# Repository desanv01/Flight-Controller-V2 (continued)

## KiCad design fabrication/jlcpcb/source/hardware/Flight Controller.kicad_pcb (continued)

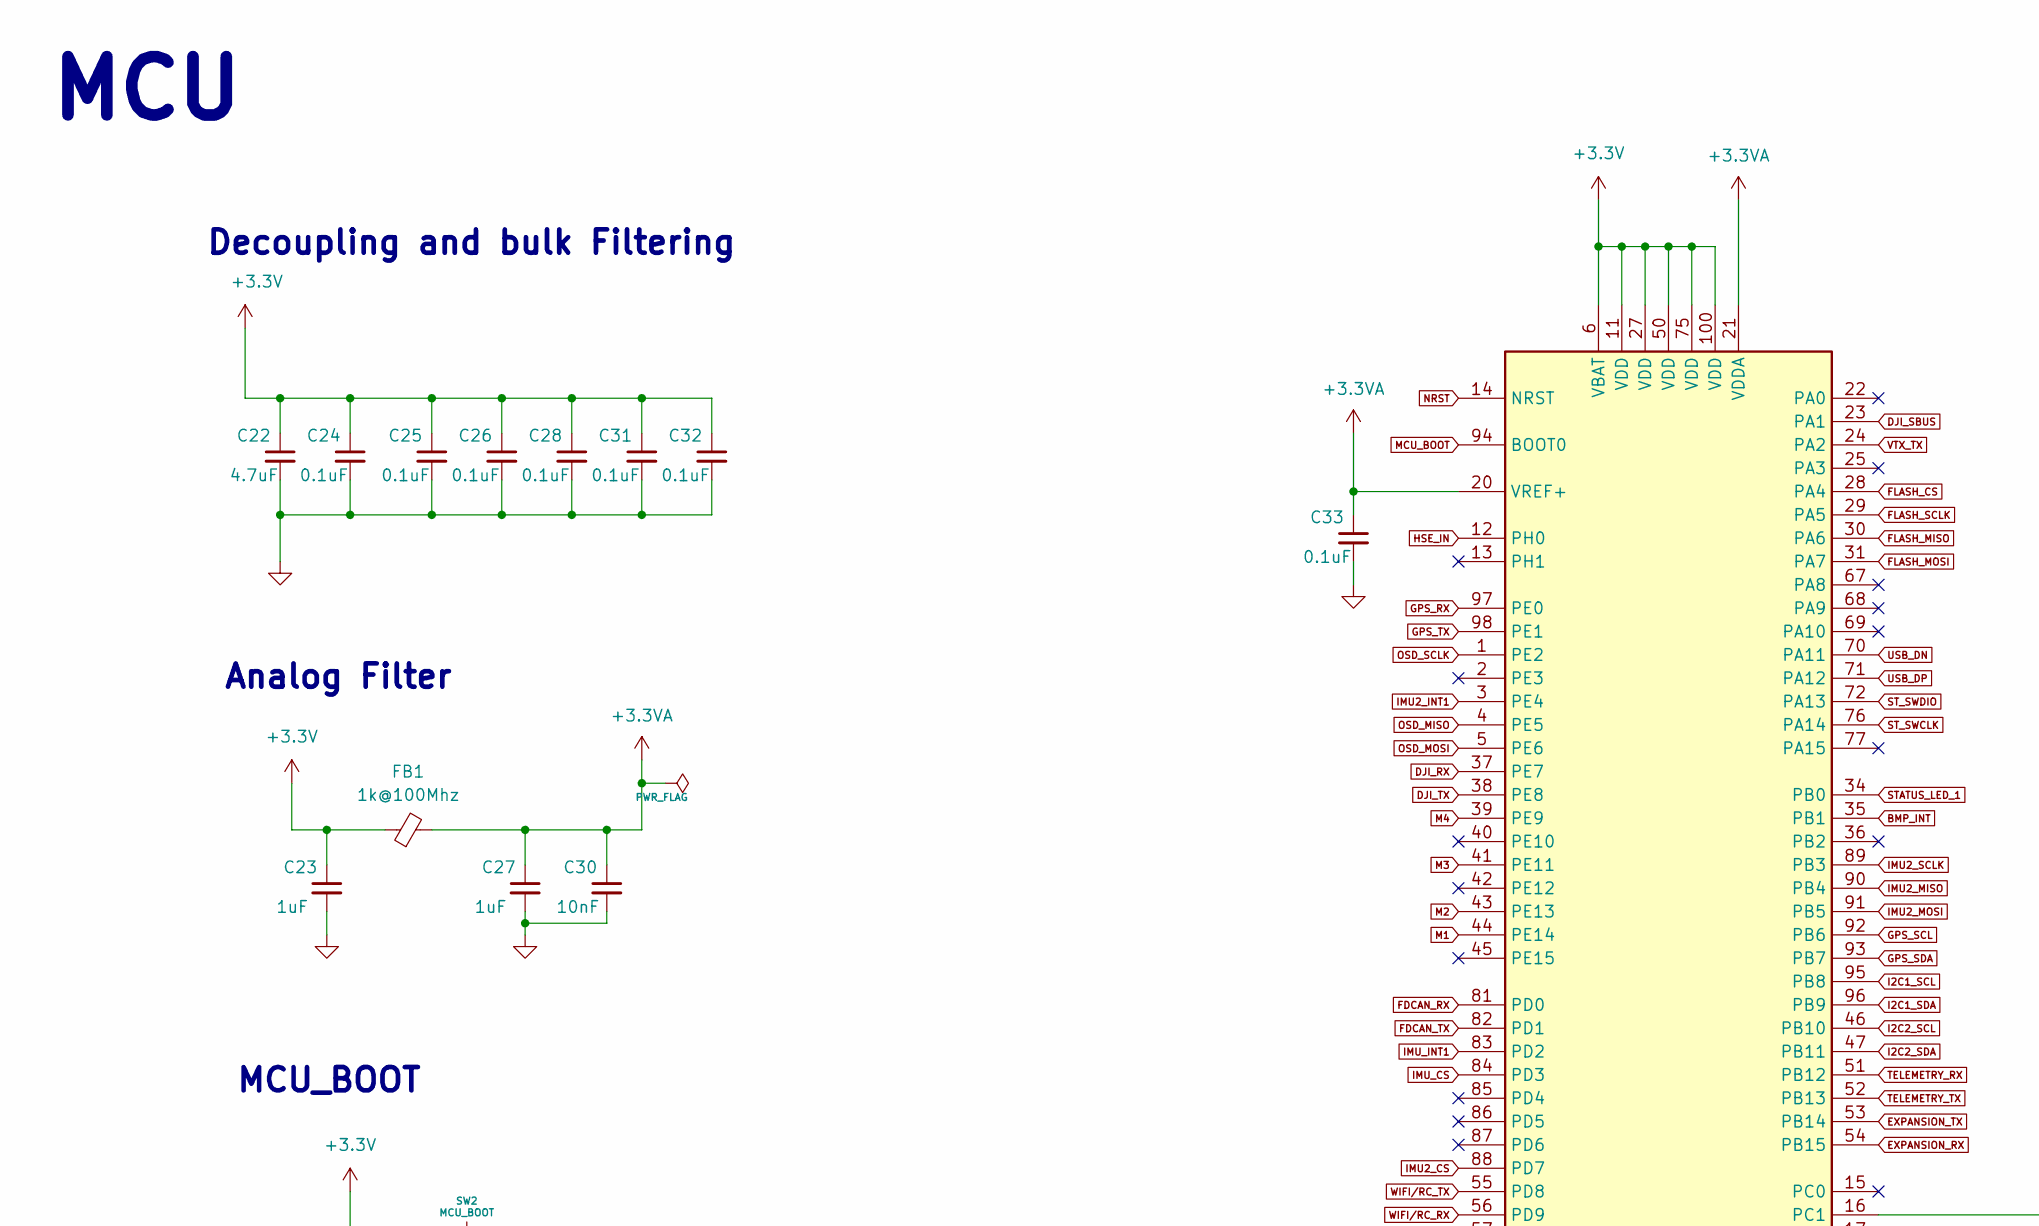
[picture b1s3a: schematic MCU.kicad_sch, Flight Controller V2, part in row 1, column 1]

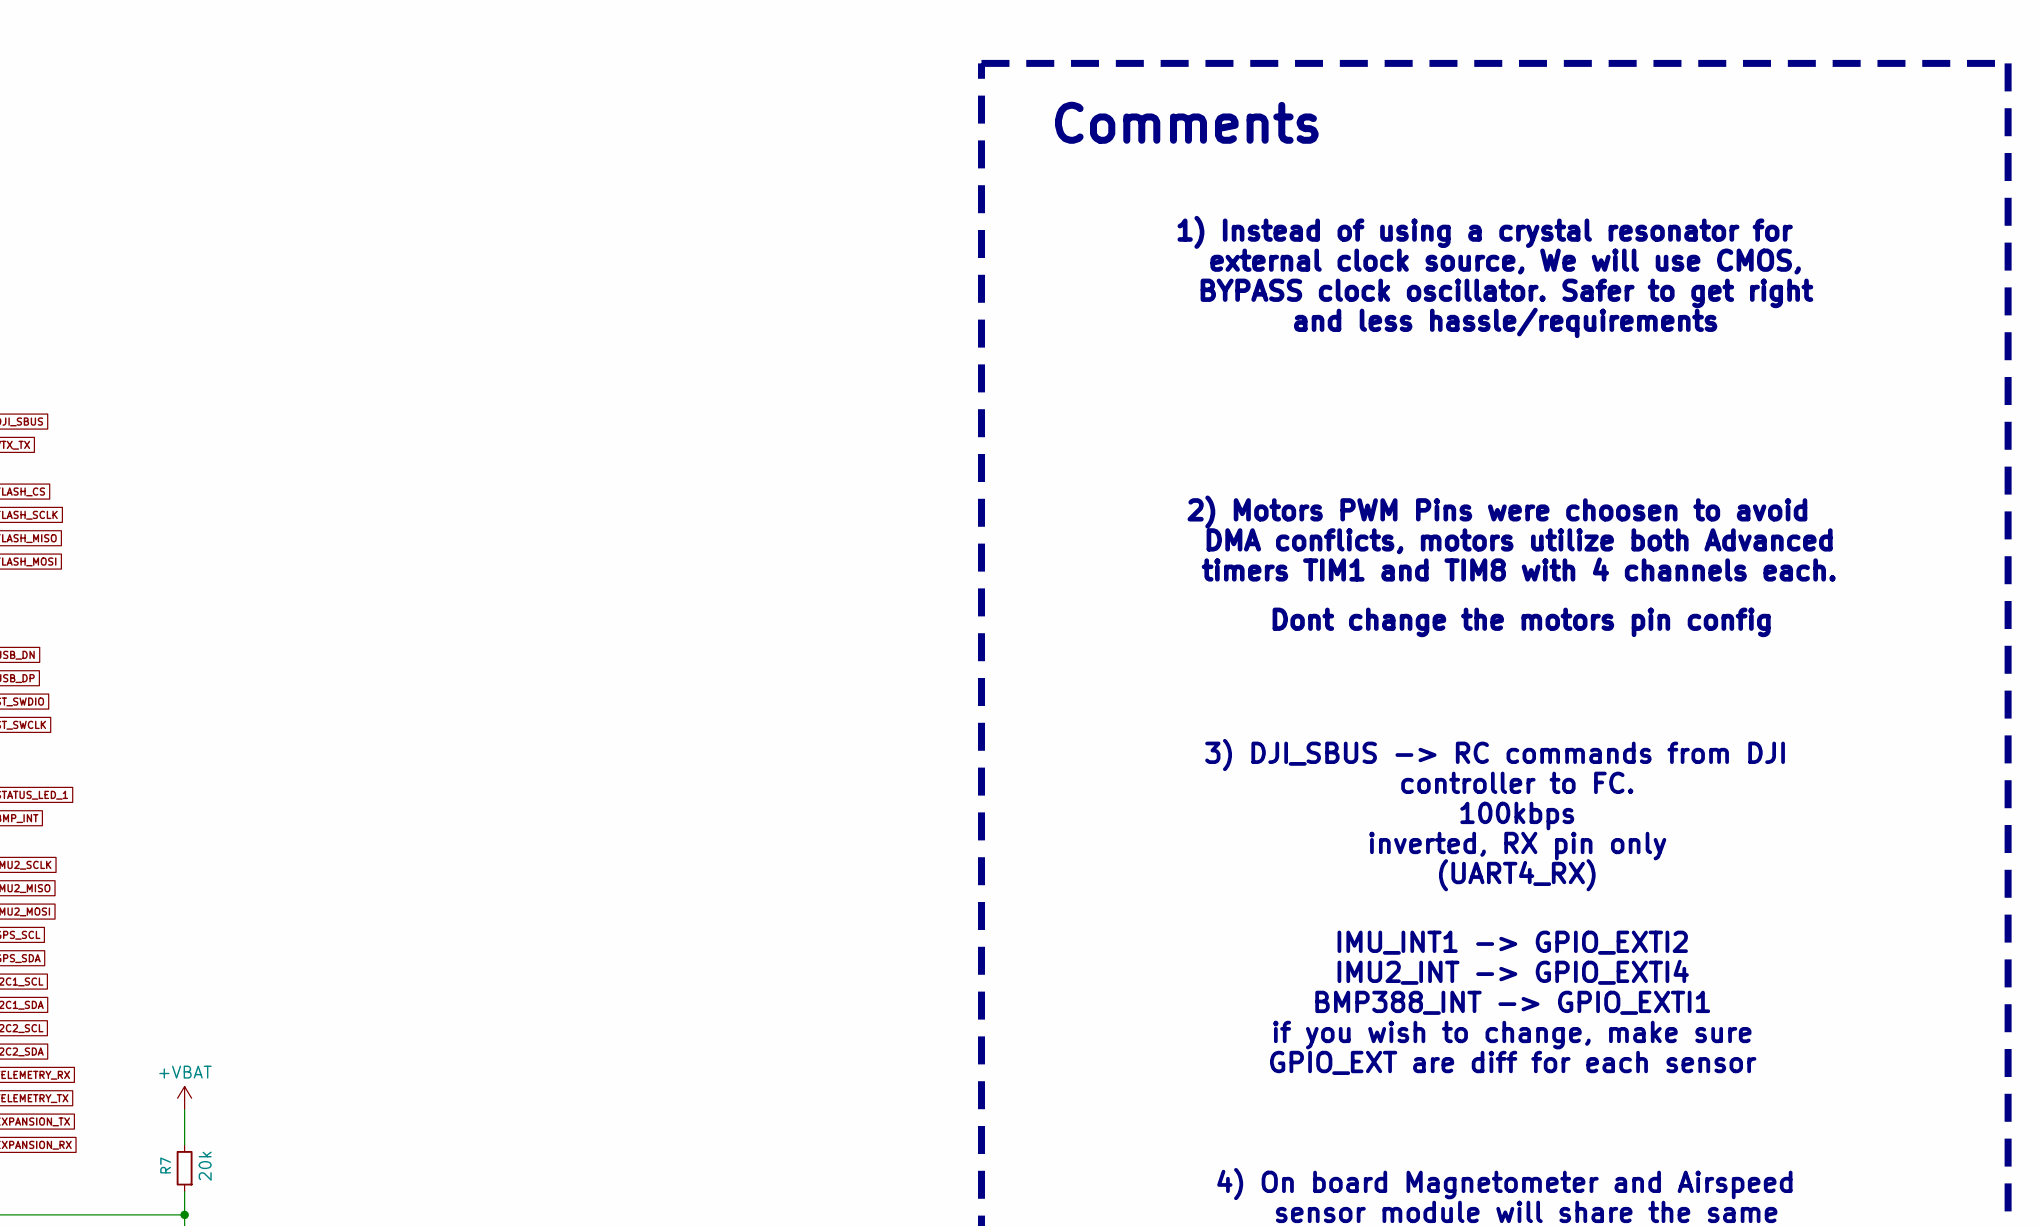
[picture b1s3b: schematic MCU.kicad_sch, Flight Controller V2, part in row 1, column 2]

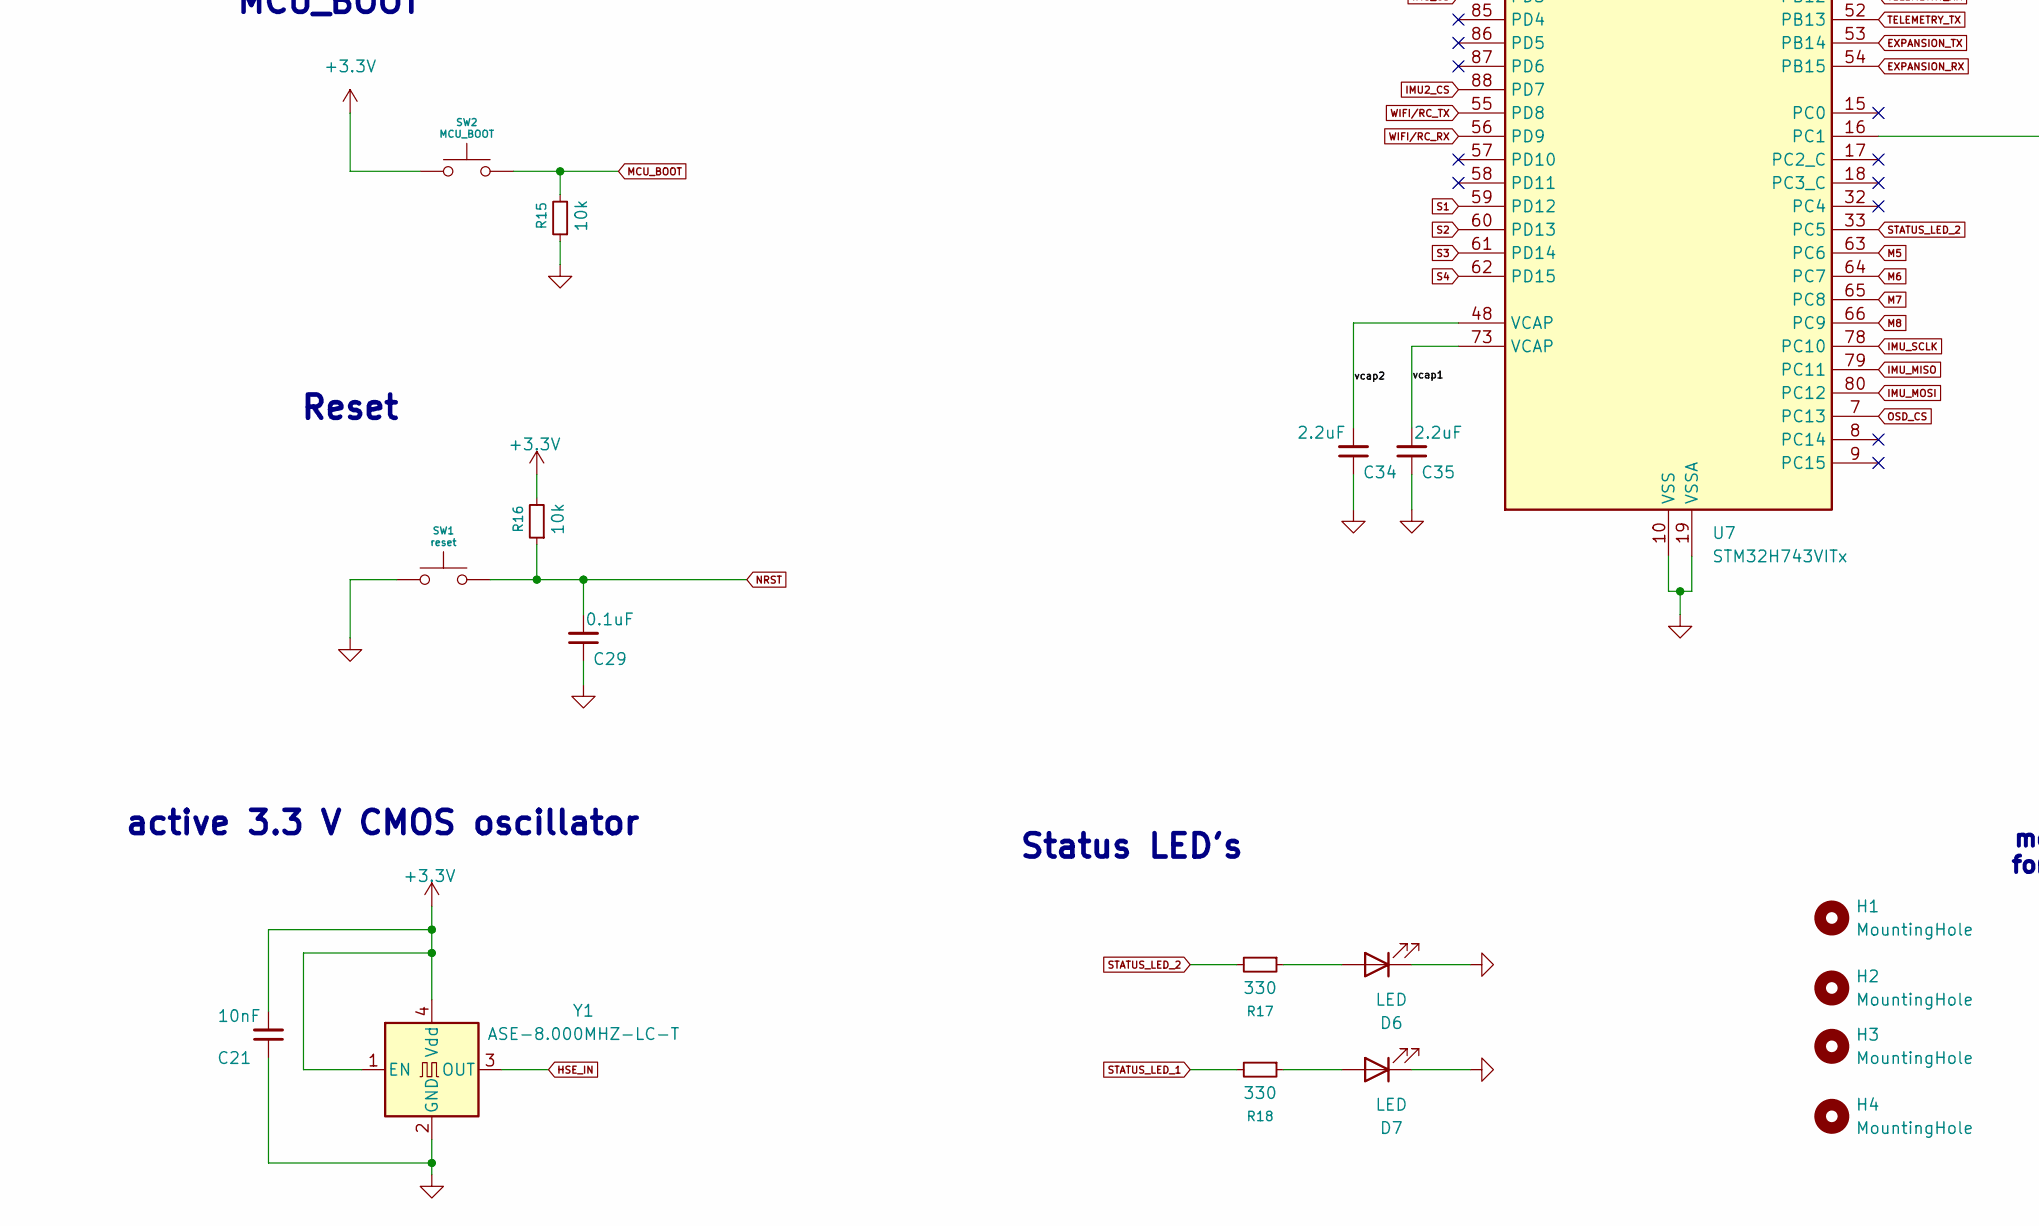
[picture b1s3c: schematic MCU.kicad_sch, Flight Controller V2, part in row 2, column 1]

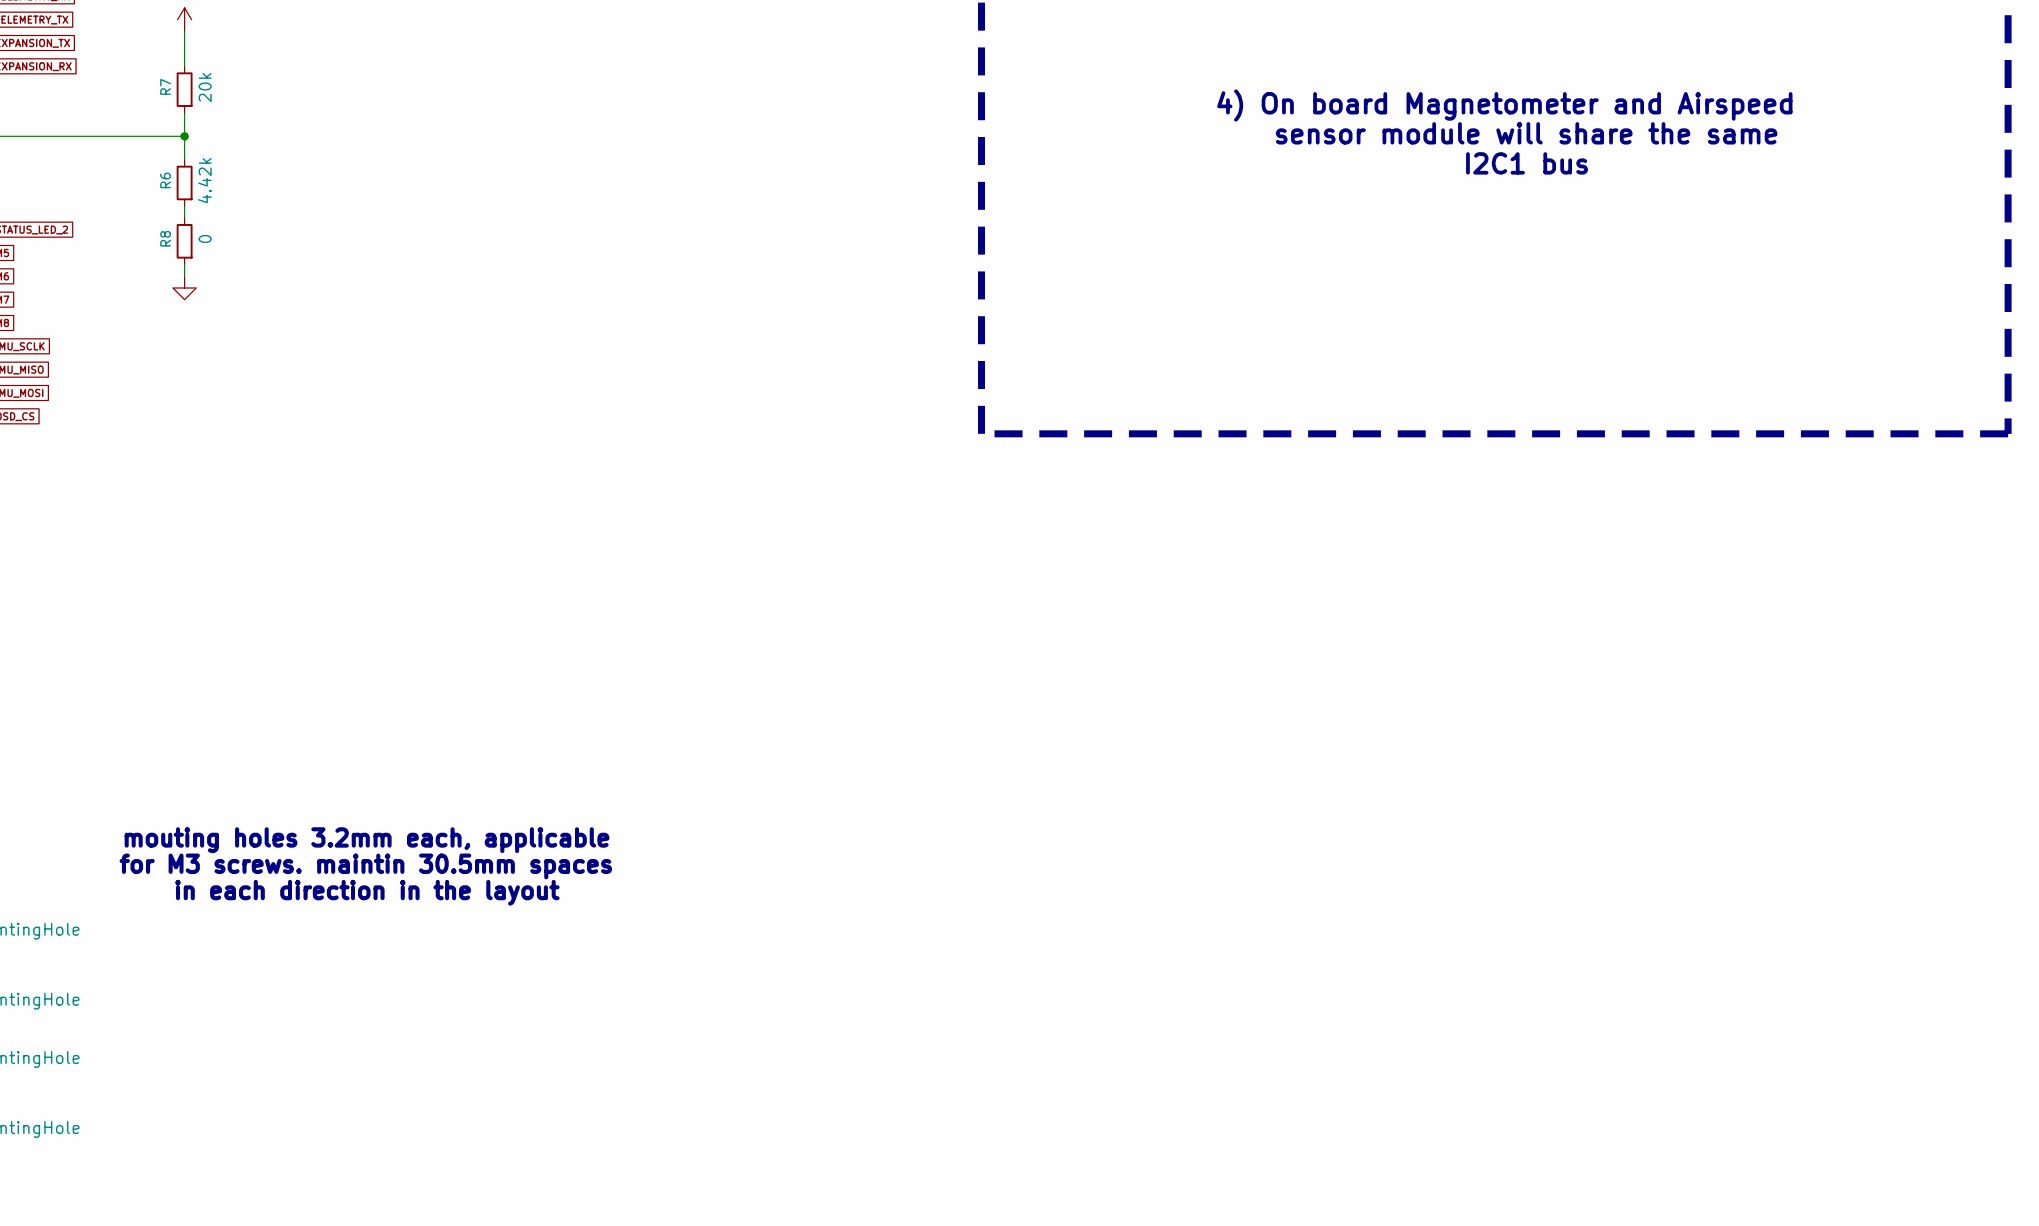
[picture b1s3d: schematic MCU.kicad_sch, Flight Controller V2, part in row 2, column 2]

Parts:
C21: 10nF; C_0603_1608Metric
C22: 4.7uF; C_0603_1608Metric
C23, C27: 1uF; C_0603_1608Metric
C24, C25, C26, C28, C29, C31, C32: 0.1uF; C_0402_1005Metric
C30: 10nF; C_0402_1005Metric
C33: 0.1uF; C_0603_1608Metric
C34, C35: 2.2uF; C_0603_1608Metric
D6, D7: LED; LED_0805_2012Metric
FB1: 1k@100Mhz; L_0603_1608Metric
H1, H2, H3, H4: MountingHole; MountingHole_3.2mm_M3_Pad_Via
R6: 4.42k; R_0402_1005Metric
R7: 20k; R_0402_1005Metric
R8: 0; R_0402_1005Metric
R15, R16: 10k; R_0402_1005Metric
R17, R18: 330; R_0402_1005Metric
SW1: reset; SW_Push_SPST_NO_Alps_SKRK
SW2: MCU_BOOT; SW_Push_SPST_NO_Alps_SKRK
U7: STM32H743VITx; LQFP-100_14x14mm_P0.5mm
Y1: ASE-8.000MHZ-LC-T; Oscillator_SMD_Abracon_ASE-4Pin_3.2x2.5mm

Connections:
+3.3V: C21.2, C22.1, C23.1, C24.1, C25.1, C26.1, C28.1, C31.1, C32.1, FB1.1, R16.2, SW2.1, U7.6 (VBAT), U7.11 (VDD), U7.27 (VDD), U7.50 (VDD), U7.75 (VDD), U7.100 (VDD), Y1.1 (EN), Y1.4 (Vdd); also elsewhere on the board
+3.3VA: C27.1, C30.1, C33.1, FB1.2, U7.20 (VREF+), U7.21 (VDDA)
+VBAT: R7.2; also elsewhere on the board
/MCU/vcap1: C35.2, U7.73 (VCAP)
/MCU/vcap2: C34.2, U7.48 (VCAP)
BMP_INT: U7.35 (PB1); also elsewhere on the board
DJI_RX: U7.37 (PE7); also elsewhere on the board
DJI_SBUS: U7.23 (PA1); also elsewhere on the board
DJI_TX: U7.38 (PE8); also elsewhere on the board
EXPANSION_RX: U7.54 (PB15); also elsewhere on the board
EXPANSION_TX: U7.53 (PB14); also elsewhere on the board
FDCAN_RX: U7.81 (PD0); also elsewhere on the board
FDCAN_TX: U7.82 (PD1); also elsewhere on the board
FLASH_CS: U7.28 (PA4); also elsewhere on the board
FLASH_MISO: U7.30 (PA6); also elsewhere on the board
FLASH_MOSI: U7.31 (PA7); also elsewhere on the board
FLASH_SCLK: U7.29 (PA5); also elsewhere on the board
GND: C21.1, C22.2, C23.2, C24.2, C25.2, C26.2, C27.2, C28.2, C29.1, C30.2, C31.2, C32.2, C33.2, C34.1, C35.1, D6.1 (K), D7.1 (K), R8.1, R15.1, SW1.1, U7.10 (VSS), U7.19 (VSSA), U7.26 (VSS), U7.49 (VSS), U7.74 (VSS), U7.99 (VSS), Y1.2 (GND); also elsewhere on the board
GPS_RX: U7.97 (PE0); also elsewhere on the board
GPS_SCL: U7.92 (PB6); also elsewhere on the board
GPS_SDA: U7.93 (PB7); also elsewhere on the board
GPS_TX: U7.98 (PE1); also elsewhere on the board
HSE_IN: U7.12 (PH0), Y1.3 (OUT)
I2C1_SCL: U7.95 (PB8); also elsewhere on the board
I2C1_SDA: U7.96 (PB9); also elsewhere on the board
I2C2_SCL: U7.46 (PB10); also elsewhere on the board
I2C2_SDA: U7.47 (PB11); also elsewhere on the board
IMU2_CS: U7.88 (PD7); also elsewhere on the board
IMU2_INT1: U7.3 (PE4); also elsewhere on the board
IMU2_MISO: U7.90 (PB4); also elsewhere on the board
IMU2_MOSI: U7.91 (PB5); also elsewhere on the board
IMU2_SCLK: U7.89 (PB3); also elsewhere on the board
IMU_CS: U7.84 (PD3); also elsewhere on the board
IMU_INT1: U7.83 (PD2); also elsewhere on the board
IMU_MISO: U7.79 (PC11); also elsewhere on the board
IMU_MOSI: U7.80 (PC12); also elsewhere on the board
IMU_SCLK: U7.78 (PC10); also elsewhere on the board
M1: U7.44 (PE14); also elsewhere on the board
M2: U7.43 (PE13); also elsewhere on the board
M3: U7.41 (PE11); also elsewhere on the board
M4: U7.39 (PE9); also elsewhere on the board
M5: U7.63 (PC6); also elsewhere on the board
M6: U7.64 (PC7); also elsewhere on the board
M7: U7.65 (PC8); also elsewhere on the board
M8: U7.66 (PC9); also elsewhere on the board
MCU_BOOT: R15.2, SW2.2, U7.94 (BOOT0)
NRST: C29.2, R16.1, SW1.2, U7.14 (NRST)
unnamed: D6.2 (A), R17.1
unnamed: D7.2 (A), R18.1
unnamed: R6.1, R8.2
unnamed: R6.2, R7.1, U7.16 (PC1)
OSD_CS: U7.7 (PC13); also elsewhere on the board
OSD_MISO: U7.4 (PE5); also elsewhere on the board
OSD_MOSI: U7.5 (PE6); also elsewhere on the board
OSD_SCLK: U7.1 (PE2); also elsewhere on the board
S1: U7.59 (PD12); also elsewhere on the board
S2: U7.60 (PD13); also elsewhere on the board
S3: U7.61 (PD14); also elsewhere on the board
S4: U7.62 (PD15); also elsewhere on the board
STATUS_LED_1: R18.2, U7.34 (PB0)
STATUS_LED_2: R17.2, U7.33 (PC5)
ST_SWCLK: U7.76 (PA14); also elsewhere on the board
ST_SWDIO: U7.72 (PA13); also elsewhere on the board
TELEMETRY_RX: U7.51 (PB12); also elsewhere on the board
TELEMETRY_TX: U7.52 (PB13); also elsewhere on the board
USB_DN: U7.70 (PA11); also elsewhere on the board
USB_DP: U7.71 (PA12); also elsewhere on the board
VTX_TX: U7.24 (PA2); also elsewhere on the board
WIFI/RC_RX: U7.56 (PD9); also elsewhere on the board
WIFI/RC_TX: U7.55 (PD8); also elsewhere on the board

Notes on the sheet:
Analog Filter
Reset
4) On board Magnetometer and Airspeed sensor module will share the same I2C1 bus
mouting holes 3.2mm each, applicable for M3 screws. maintin 30.5mm spaces in each direction in the layout
1) Instead of using a crystal resonator for external clock source, We will use CMOS, BYPASS clock oscillator. Safer to get right and less hassle/requirements
Comments
MCU
2) Motors PWM Pins were choosen to avoid DMA conflicts, motors utilize both Advanced timers TIM1 and TIM8 with 4 channels each.
3) DJI_SBUS -> RC commands from DJI controller to FC. 100kbps inverted, RX pin only (UART4_RX)
MCU_BOOT
active 3.3 V CMOS oscillator
IMU_INT1 -> GPIO_EXTI2 IMU2_INT -> GPIO_EXTI4 BMP388_INT -> GPIO_EXTI1 if you wish to change, make sure GPIO_EXT are diff for each sensor
Dont change the motors pin config
Decoupling and bulk Filtering
Status LED's

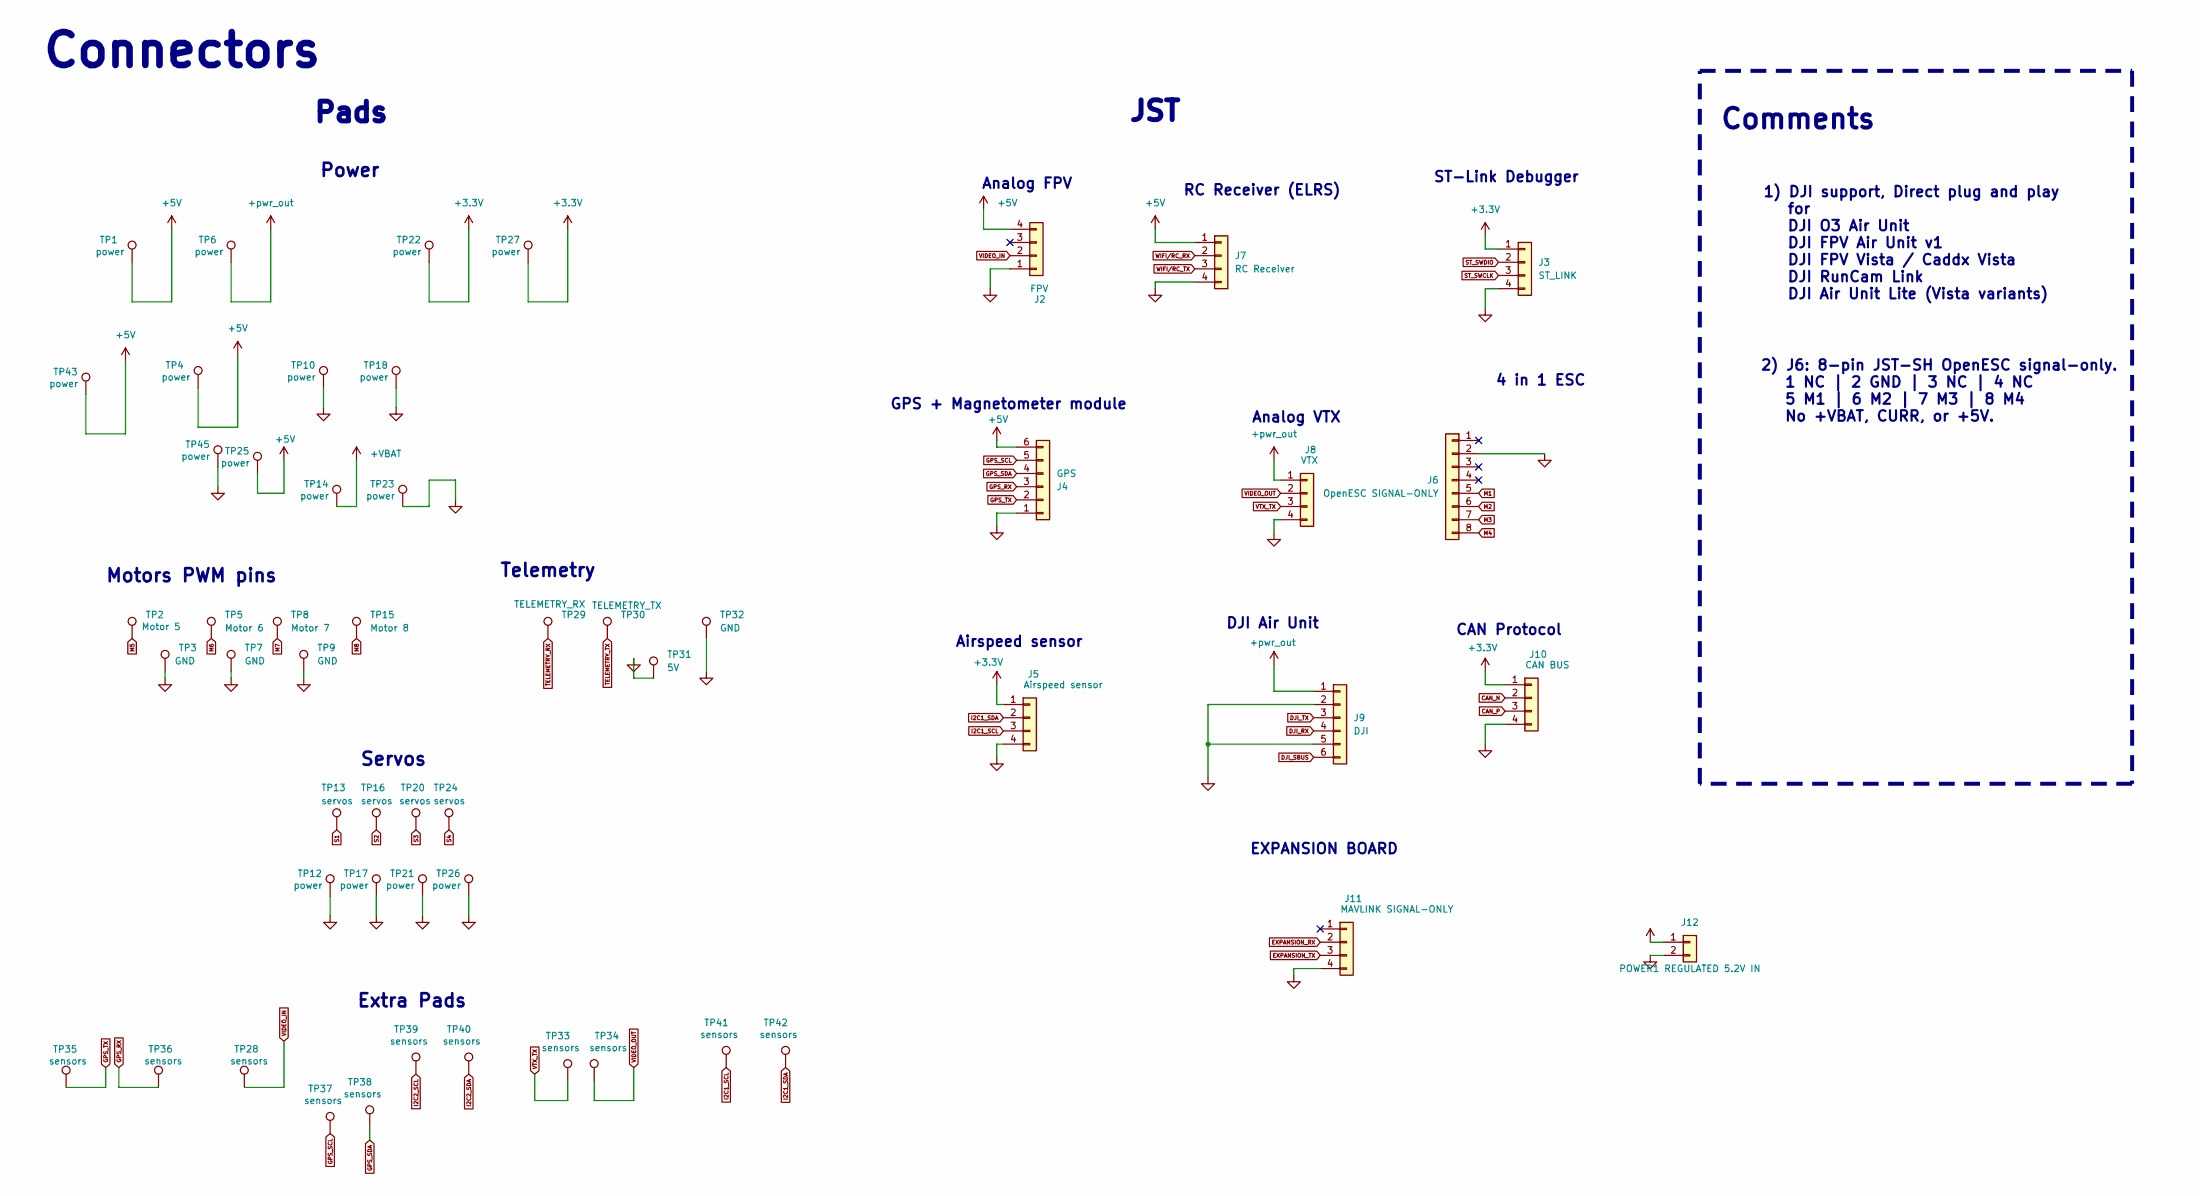
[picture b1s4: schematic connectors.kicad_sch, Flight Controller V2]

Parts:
J2: FPV; CONN-SMD_4P-P1.00_SM04B-SRSS-TB-LF-SN
J3: ST_LINK; CONN-SMD_4P-P1.00_SM04B-SRSS-TB-LF-SN
J4: GPS; JST_SH_SM06B-SRSS-TB_1x06-1MP_P1.00mm_Horizontal
J5: Airspeed sensor; CONN-SMD_4P-P1.00_SM04B-SRSS-TB-LF-SN
J6: OpenESC SIGNAL-ONLY; JST_SH_SM08B-SRSS-TB_1x08-1MP_P1.00mm_Horizontal
J7: RC Receiver; CONN-SMD_4P-P1.00_SM04B-SRSS-TB-LF-SN
J8: VTX; CONN-SMD_4P-P1.00_SM04B-SRSS-TB-LF-SN
J9: DJI; JST_SH_SM06B-SRSS-TB_1x06-1MP_P1.00mm_Horizontal
J10: CAN BUS; CONN-SMD_4P-P1.00_SM04B-SRSS-TB-LF-SN
J11: MAVLINK SIGNAL-ONLY; CONN-SMD_4P-P1.00_SM04B-SRSS-TB-LF-SN
J12: POWER1 REGULATED 5.2V IN; Molex_Nano-Fit_105311-1202_1x02_P2.50mm_Vertical_SolderClip; MPN 105311-1202
TP1, TP4, TP6, TP10, TP12, TP17, TP18, TP21, TP22, TP25, TP26, TP27, TP43, TP45: power; Solderpad
TP2: Motor 5; Solderpad
TP3, TP7, TP9, TP32: GND; Solderpad
TP5: Motor 6; Solderpad
TP8: Motor 7; Solderpad
TP13, TP16, TP20, TP24: servos; Solderpad
TP14, TP23: power; BAT pad
TP15: Motor 8; Solderpad
TP28, TP33, TP34, TP35, TP36, TP37, TP38, TP39, TP40, TP41, TP42: sensors; Solderpad
TP29: TELEMETRY_RX; Solderpad
TP30: TELEMETRY_TX; Solderpad
TP31: 5V; Solderpad

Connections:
+3.3V: J3.1, J5.1, J10.1, TP22.1 (1_1), TP27.1 (1_1); also elsewhere on the board
+5V: J2.4, J4.6, J7.1, J12.1, TP1.1 (1_1), TP4.1 (1_1), TP25.1 (1_1), TP43.1 (1_1); also elsewhere on the board
+VBAT: TP14.1 (1_1); also elsewhere on the board
+pwr_out: J8.1, J9.1, TP6.1 (1_1); also elsewhere on the board
CAN_N: J10.2; also elsewhere on the board
CAN_P: J10.3; also elsewhere on the board
DJI_RX: J9.4; also elsewhere on the board
DJI_SBUS: J9.6; also elsewhere on the board
DJI_TX: J9.3; also elsewhere on the board
EXPANSION_RX: J11.2; also elsewhere on the board
EXPANSION_TX: J11.3; also elsewhere on the board
GND: J2.1, J3.4, J4.1, J5.4, J6.2, J7.4, J8.4, J9.2, J9.5, J10.4, J11.4, J12.2, TP3.1 (1_1), TP7.1 (1_1), TP9.1 (1_1), TP10.1 (1_1), TP12.1 (1_1), TP17.1 (1_1), TP18.1 (1_1), TP21.1 (1_1), TP23.1 (1_1), TP26.1 (1_1), TP31.1 (1_1), TP32.1 (1_1), TP45.1 (1_1); also elsewhere on the board
GPS_RX: J4.3, TP36.1 (1_1); also elsewhere on the board
GPS_SCL: J4.5, TP37.1 (1_1); also elsewhere on the board
GPS_SDA: J4.4, TP38.1 (1_1); also elsewhere on the board
GPS_TX: J4.2, TP35.1 (1_1); also elsewhere on the board
I2C1_SCL: J5.3, TP41.1 (1_1); also elsewhere on the board
I2C1_SDA: J5.2, TP42.1 (1_1); also elsewhere on the board
I2C2_SCL: TP39.1 (1_1); also elsewhere on the board
I2C2_SDA: TP40.1 (1_1); also elsewhere on the board
M1: J6.5; also elsewhere on the board
M2: J6.6; also elsewhere on the board
M3: J6.7; also elsewhere on the board
M4: J6.8; also elsewhere on the board
M5: TP2.1 (1_1); also elsewhere on the board
M6: TP5.1 (1_1); also elsewhere on the board
M7: TP8.1 (1_1); also elsewhere on the board
M8: TP15.1 (1_1); also elsewhere on the board
S1: TP13.1 (1_1); also elsewhere on the board
S2: TP16.1 (1_1); also elsewhere on the board
S3: TP20.1 (1_1); also elsewhere on the board
S4: TP24.1 (1_1); also elsewhere on the board
ST_SWCLK: J3.3; also elsewhere on the board
ST_SWDIO: J3.2; also elsewhere on the board
TELEMETRY_RX: TP29.1 (1_1); also elsewhere on the board
TELEMETRY_TX: TP30.1 (1_1); also elsewhere on the board
VIDEO_IN: J2.2, TP28.1 (1_1); also elsewhere on the board
VIDEO_OUT: J8.2, TP34.1 (1_1); also elsewhere on the board
VTX_TX: J8.3, TP33.1 (1_1); also elsewhere on the board
WIFI/RC_RX: J7.2; also elsewhere on the board
WIFI/RC_TX: J7.3; also elsewhere on the board

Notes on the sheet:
Servos
JST
RC Receiver (ELRS)
ST-Link Debugger
GPS + Magnetometer module
4 in 1 ESC
Power
Telemetry
CAN Protocol
EXPANSION BOARD
Comments
Airspeed sensor
2) J6: 8-pin JST-SH OpenESC signal-only. 1 NC | 2 GND | 3 NC | 4 NC 5 M1 | 6 M2 | 7 M3 | 8 M4 No +VBAT, CURR, or +5V.
1) DJI support, Direct plug and play for DJI O3 Air Unit DJI FPV Air Unit v1 DJI FPV Vista / Caddx Vista DJI RunCam Link DJI Air Unit Lite (Vista variants)
Extra Pads
Analog VTX
DJI Air Unit
Connectors
Pads
Analog FPV
Motors PWM pins

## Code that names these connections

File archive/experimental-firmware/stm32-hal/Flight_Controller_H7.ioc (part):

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Mcu.Name=STM32H743VITx
Mcu.Package=LQFP100
Mcu.UserName=STM32H743VITx
PA0.GPIOParameters=PinAttribute
PA0.Mode=Asynchronous
PA0.PinAttribute=Free
PA0.Signal=UART4_TX
PA1.GPIOParameters=GPIO_Label,PinAttribute
PA1.GPIO_Label=DJI_SBUS
PA1.Mode=Asynchronous
PA1.PinAttribute=Free
PA1.Signal=UART4_RX
PA11.GPIOParameters=PinAttribute
PA11.Mode=Device_Only
PA11.PinAttribute=Free
PA11.Signal=USB_OTG_FS_DM
PA12.GPIOParameters=PinAttribute
PA12.Mode=Device_Only
PA12.PinAttribute=Free
PA12.Signal=USB_OTG_FS_DP
PA13\ (JTMS/SWDIO).GPIOParameters=PinAttribute
PA13\ (JTMS/SWDIO).Mode=Serial_Wire
PA13\ (JTMS/SWDIO).PinAttribute=Free
PA13\ (JTMS/SWDIO).Signal=DEBUG_JTMS-SWDIO
PA14\ (JTCK/SWCLK).GPIOParameters=PinAttribute
PA14\ (JTCK/SWCLK).Mode=Serial_Wire
PA14\ (JTCK/SWCLK).PinAttribute=Free
PA14\ (JTCK/SWCLK).Signal=DEBUG_JTCK-SWCLK
PA2.GPIOParameters=GPIO_Label,PinAttribute
PA2.GPIO_Label=VTX_TX
PA2.Mode=Asynchronous
PA2.PinAttribute=Free
PA2.Signal=USART2_TX
PA3.GPIOParameters=GPIO_Label,PinAttribute
PA3.GPIO_Label=VTX_RX
PA3.Mode=Asynchronous
PA3.PinAttribute=Free
PA3.Signal=USART2_RX
PA4.GPIOParameters=GPIO_Label,PinAttribute
PA4.GPIO_Label=FLASH_CS
PA4.PinAttribute=Free
PA4.Signal=GPIO_Output
PA5.GPIOParameters=GPIO_Label,PinAttribute
PA5.GPIO_Label=FLASH_SCK
PA5.Mode=Full_Duplex_Master
PA5.PinAttribute=Free
PA5.Signal=SPI1_SCK
PA6.GPIOParameters=GPIO_Label,PinAttribute
PA6.GPIO_Label=FLASH_MISO
PA6.Mode=Full_Duplex_Master
PA6.PinAttribute=Free
PA6.Signal=SPI1_MISO
PA7.GPIOParameters=GPIO_Label,PinAttribute
PA7.GPIO_Label=FLASH_MOSI
PA7.Mode=Full_Duplex_Master
PA7.PinAttribute=Free
PA7.Signal=SPI1_MOSI
PB0.GPIOParameters=PinState,GPIO_Label,PinAttribute
PB0.GPIO_Label=STATUS_LED_1
PB0.PinAttribute=Free
PB0.PinState=GPIO_PIN_SET
PB0.Signal=GPIO_Output
PB1.GPIOParameters=GPIO_Label,PinAttribute
PB1.GPIO_Label=BMP_INT1
PB1.PinAttribute=Free
PB1.Signal=GPXTI1
PB10.GPIOParameters=PinAttribute
PB10.Mode=I2C
PB10.PinAttribute=Free
PB10.Signal=I2C2_SCL
PB11.GPIOParameters=PinAttribute
PB11.Mode=I2C
PB11.PinAttribute=Free
PB11.Signal=I2C2_SDA
PB12.GPIOParameters=GPIO_Label,PinAttribute
PB12.GPIO_Label=TELEMETRY_RX
PB12.Mode=Asynchronous
PB12.PinAttribute=Free
PB12.Signal=UART5_RX
PB13.GPIOParameters=GPIO_Label,PinAttribute
PB13.GPIO_Label=TELEMETRY_TX
PB13.Mode=Asynchronous
PB13.PinAttribute=Free
PB13.Signal=UART5_TX
PB14.GPIOParameters=GPIO_Label,PinAttribute
PB14.GPIO_Label=Expansion_TX
PB14.Mode=Asynchronous
PB14.PinAttribute=Free
PB14.Signal=USART1_TX
PB15.GPIOParameters=GPIO_Label,PinAttribute
PB15.GPIO_Label=Expansion_RX
PB15.Mode=Asynchronous
PB15.PinAttribute=Free
PB15.Signal=USART1_RX
PB3\ (JTDO/TRACESWO).GPIOParameters=GPIO_Label,PinAttribute
PB3\ (JTDO/TRACESWO).GPIO_Label=IMU2_SCLK
PB3\ (JTDO/TRACESWO).Mode=Full_Duplex_Master
PB3\ (JTDO/TRACESWO).PinAttribute=Free
PB3\ (JTDO/TRACESWO).Signal=SPI6_SCK
PB4\ (NJTRST).GPIOParameters=GPIO_Label,PinAttribute
PB4\ (NJTRST).GPIO_Label=IMU2_MISO
PB4\ (NJTRST).Mode=Full_Duplex_Master
PB4\ (NJTRST).PinAttribute=Free
PB4\ (NJTRST).Signal=SPI6_MISO
PB5.GPIOParameters=GPIO_Label,PinAttribute
PB5.GPIO_Label=IMU2_MOSI
PB5.Mode=Full_Duplex_Master
PB5.PinAttribute=Free
PB5.Signal=SPI6_MOSI
PB6.GPIOParameters=GPIO_Label,PinAttribute
PB6.GPIO_Label=GPS_SCL
PB6.Mode=I2C
PB6.PinAttribute=Free
PB6.Signal=I2C4_SCL
PB7.GPIOParameters=GPIO_Label,PinAttribute
PB7.GPIO_Label=GPS_SDA
PB7.Mode=I2C
PB7.PinAttribute=Free
PB7.Signal=I2C4_SDA
PB8.GPIOParameters=PinAttribute
PB8.Mode=I2C
PB8.PinAttribute=Free
PB8.Signal=I2C1_SCL
PB9.GPIOParameters=PinAttribute
PB9.Mode=I2C
PB9.PinAttribute=Free
PB9.Signal=I2C1_SDA
PC1.GPIOParameters=GPIO_Label,PinAttribute
PC1.GPIO_Label=ADC_VOLTAGE
PC1.PinAttribute=Free
PC1.Signal=ADCx_INP11
PC10.GPIOParameters=GPIO_Label,PinAttribute
PC10.GPIO_Label=IMU_SCLK
PC10.Mode=Full_Duplex_Master
PC10.PinAttribute=Free
PC10.Signal=SPI3_SCK
PC11.GPIOParameters=GPIO_Label,PinAttribute
PC11.GPIO_Label=IMU_MISO
PC11.Mode=Full_Duplex_Master
PC11.PinAttribute=Free
PC11.Signal=SPI3_MISO
PC12.GPIOParameters=GPIO_Label,PinAttribute
PC12.GPIO_Label=IMU_MOSI
PC12.Mode=Full_Duplex_Master
PC12.PinAttribute=Free
PC12.Signal=SPI3_MOSI
PC13.GPIOParameters=GPIO_Label,PinAttribute
PC13.GPIO_Label=OSD_CS
PC13.PinAttribute=Free
PC13.Signal=GPIO_Output
PC3_C.GPIOParameters=GPIO_Label,PinAttribute
PC3_C.GPIO_Label=ADC_CURR
PC3_C.Mode=IN1-Single-Ended
PC3_C.PinAttribute=Free
PC3_C.Signal=ADC3_INP1
PC5.GPIOParameters=PinState,GPIO_Label,PinAttribute
PC5.GPIO_Label=STATUS_LED_2
PC5.PinAttribute=Free
PC5.PinState=GPIO_PIN_SET
PC5.Signal=GPIO_Output
PC6.GPIOParameters=GPIO_Label,PinAttribute
PC6.GPIO_Label=M5
PC6.PinAttribute=Free
PC6.Signal=S_TIM8_CH1
PC7.GPIOParameters=GPIO_Label,PinAttribute
PC7.GPIO_Label=M6
PC7.PinAttribute=Free
PC7.Signal=S_TIM8_CH2
PC8.GPIOParameters=GPIO_Label,PinAttribute
PC8.GPIO_Label=M7
PC8.PinAttribute=Free
PC8.Signal=S_TIM8_CH3
PC9.GPIOParameters=GPIO_Label,PinAttribute
PC9.GPIO_Label=M8
PC9.PinAttribute=Free
PC9.Signal=S_TIM8_CH4
PD0.GPIOParameters=PinAttribute
PD0.Mode=FDCAN_Activate
PD0.PinAttribute=Free
PD0.Signal=FDCAN1_RX
PD1.GPIOParameters=PinAttribute
PD1.Mode=FDCAN_Activate
PD1.PinAttribute=Free
PD1.Signal=FDCAN1_TX
PD12.GPIOParameters=GPIO_Label,PinAttribute
PD12.GPIO_Label=S1
PD12.PinAttribute=Free
PD12.Signal=S_TIM4_CH1
PD13.GPIOParameters=GPIO_Label,PinAttribute
PD13.GPIO_Label=S2
PD13.PinAttribute=Free
PD13.Signal=S_TIM4_CH2
PD14.GPIOParameters=GPIO_Label,PinAttribute
PD14.GPIO_Label=S3
PD14.PinAttribute=Free
PD14.Signal=S_TIM4_CH3
PD15.GPIOParameters=GPIO_Label,PinAttribute
PD15.GPIO_Label=S4
PD15.PinAttribute=Free
PD15.Signal=S_TIM4_CH4
PD2.GPIOParameters=GPIO_Label,PinAttribute
PD2.GPIO_Label=IMU_INT1
PD2.PinAttribute=Free
PD2.Signal=GPXTI2
PD3.GPIOParameters=GPIO_Label,PinAttribute
PD3.GPIO_Label=IMU_CS
PD3.PinAttribute=Free
PD3.Signal=GPIO_Output
PD7.GPIOParameters=GPIO_Label,PinAttribute
PD7.GPIO_Label=IMU2_CS
PD7.PinAttribute=Free
PD7.Signal=GPIO_Output
PD8.GPIOParameters=GPIO_Label,PinAttribute
PD8.GPIO_Label=WIFI/RC_TX
PD8.Mode=Asynchronous
PD8.PinAttribute=Free
PD8.Signal=USART3_TX
PD9.GPIOParameters=GPIO_Label,PinAttribute
PD9.GPIO_Label=WIFI/RC_RX
PD9.Mode=Asynchronous
PD9.PinAttribute=Free
PD9.Signal=USART3_RX
PE0.GPIOParameters=GPIO_Label,PinAttribute
PE0.GPIO_Label=GPS_RX
PE0.Mode=Asynchronous
PE0.PinAttribute=Free
PE0.Signal=UART8_RX
PE1.GPIOParameters=GPIO_Label,PinAttribute
PE1.GPIO_Label=GPS_TX
PE1.Mode=Asynchronous
PE1.PinAttribute=Free
PE1.Signal=UART8_TX
PE11.GPIOParameters=GPIO_Label,PinAttribute
PE11.GPIO_Label=M3
PE11.PinAttribute=Free
PE11.Signal=S_TIM1_CH2
PE13.GPIOParameters=GPIO_Label,PinAttribute
PE13.GPIO_Label=M2
PE13.PinAttribute=Free
PE13.Signal=S_TIM1_CH3
PE14.GPIOParameters=GPIO_Label,PinAttribute
PE14.GPIO_Label=M1
PE14.PinAttribute=Free
PE14.Signal=S_TIM1_CH4
PE2.GPIOParameters=GPIO_Label,PinAttribute
PE2.GPIO_Label=OSD_SCK
PE2.Mode=Full_Duplex_Master
PE2.PinAttribute=Free
PE2.Signal=SPI4_SCK
PE4.GPIOParameters=GPIO_Label,PinAttribute
PE4.GPIO_Label=IMU2_INT
PE4.PinAttribute=Free
PE4.Signal=GPXTI4
PE5.GPIOParameters=GPIO_Label,PinAttribute
PE5.GPIO_Label=OSD_MISO
PE5.Mode=Full_Duplex_Master
PE5.PinAttribute=Free
PE5.Signal=SPI4_MISO
PE6.GPIOParameters=GPIO_Label,PinAttribute
PE6.GPIO_Label=OSD_MOSI
PE6.Mode=Full_Duplex_Master
PE6.PinAttribute=Free
PE6.Signal=SPI4_MOSI
PE7.GPIOParameters=GPIO_Label,PinAttribute
PE7.GPIO_Label=DJI_RX
PE7.Mode=Asynchronous
PE7.PinAttribute=Free
PE7.Signal=UART7_RX
PE8.GPIOParameters=GPIO_Label,PinAttribute
PE8.GPIO_Label=DJI_TX
PE8.Mode=Asynchronous
PE8.PinAttribute=Free
PE8.Signal=UART7_TX
PE9.GPIOParameters=GPIO_Label,PinAttribute
PE9.GPIO_Label=M4
PE9.PinAttribute=Free
PE9.Signal=S_TIM1_CH1
PH0-OSC_IN\ (PH0).GPIOParameters=PinAttribute
PH0-OSC_IN\ (PH0).Mode=HSE-External-Clock-Source
PH0-OSC_IN\ (PH0).PinAttribute=Free
PH0-OSC_IN\ (PH0).Signal=RCC_OSC_IN
RCC.HSE_VALUE=8000000
RCC.SYSCLKFreq_VALUE=240000000
RCC.SYSCLKSource=RCC_SYSCLKSOURCE_PLLCLK
board=custom
